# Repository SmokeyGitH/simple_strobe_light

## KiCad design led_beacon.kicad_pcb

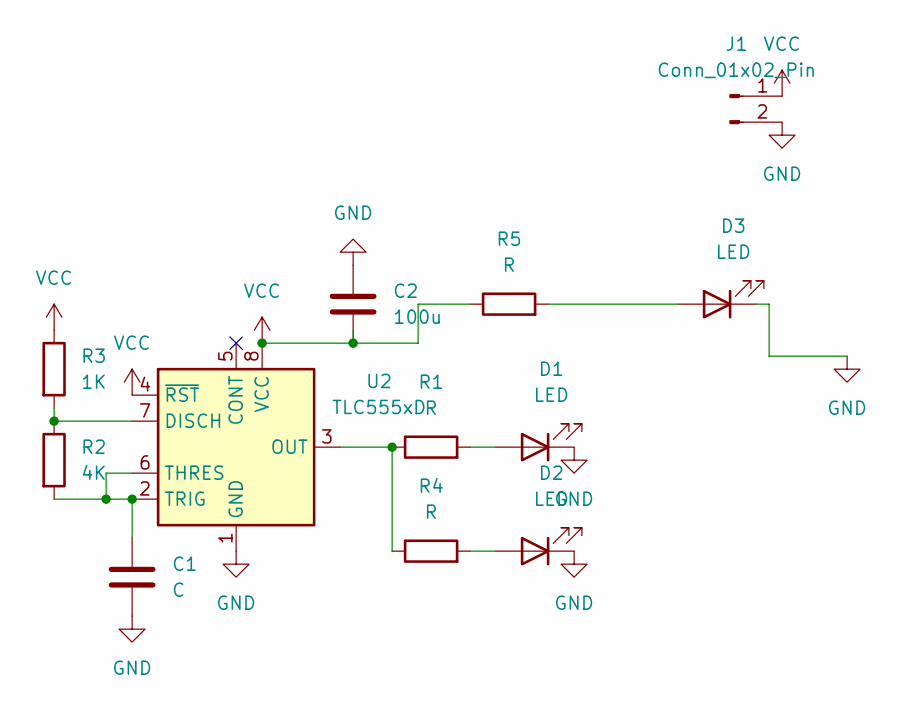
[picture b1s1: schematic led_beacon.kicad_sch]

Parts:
C1: C; C_0805_2012Metric_Pad1.18x1.45mm_HandSolder
C2: 100u; C_0805_2012Metric_Pad1.18x1.45mm_HandSolder
D1, D2: LED; LED_PLCC_2835_Handsoldering
D3: LED; LED_0805_2012Metric_Pad1.15x1.40mm_HandSolder
J1: Conn_01x02_Pin; PinHeader_1x02_P2.54mm_Vertical
R1, R4, R5: R; R_0805_2012Metric_Pad1.20x1.40mm_HandSolder
R2: 4K; R_0805_2012Metric_Pad1.20x1.40mm_HandSolder
R3: 1K; R_0805_2012Metric_Pad1.20x1.40mm_HandSolder
U2: TLC555xD; SOIC-8_3.9x4.9mm_P1.27mm

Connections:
GND: C1.2, C2.1, D1.1 (K), D2.1 (K), D3.1 (K), J1.2, U2.1 (GND)
unnamed: D1.2 (A), R1.2
unnamed: D2.2 (A), R4.2
unnamed: D3.2 (A), R5.2
unnamed: R2.1, R3.2, U2.7 (DISCH)
unnamed: R1.1, R4.1, U2.3 (OUT)
unnamed: C1.1, R2.2, U2.2 (TRIG), U2.6 (THRES)
VCC: C2.2, J1.1, R3.1, R5.1, U2.4 (~RST), U2.8 (VCC)

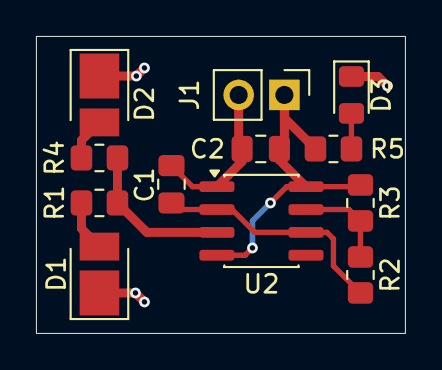
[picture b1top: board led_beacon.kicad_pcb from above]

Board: 2 copper layers, 20.5 x 16.5 mm, 12 parts (0 on the bottom side), 8 nets.
